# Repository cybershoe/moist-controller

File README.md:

# moist-controller
[![CC BY-SA 4.0][cc-by-sa-shield]][cc-by-sa]

## Overview

The Moisture-Optimization through Solar Technology (MOiST) Controller is a distributed, solar-powered, ESP8266-based
controller that exposes standard irrigation valves into [Home Assistant](https://www.home-assistant.io/) through
the [ESPHome](https://esphome.io/) component.

The MOiST valve is designed to be:

### Simple

The controller does one thing: control a valve. Once added into Home Assistant, the controller exposeses a switch that
opens or closes the valve, sensors for water flow rate and total water consumption, and battery power monitoring. That's
it. You are free to use whatever mechanism you want to manage the valves, including HA automations, Node-RED flows, or
any other platform that integratges with Home Assistant.

### Flexible

This project started because we change up our gardens frequently, and we couldn't predict in advance where we would want
automatic irrigation, or how the yard would be zoned. The idea behind the controller is that you can mount your valve, 
controller, and solar panel on a stake, stick it in the ground where you need it, point it South (or North if you're in
the Southern Hemisphere), hook it up to a hose and be up and running quickly. Buried valves with hardwired power look
nicer, and would be more appropriate for a lawn, but for a food garden, this design provides more flexibility. The
controller should be able to drive any standard irrigation valve that uses a 9V DC latching solenoid.

### Self-contained

Running hoses is one thing, running power is another. The controller was designed to minimize power consumption to a
point where it can run off of a 5-Watt, 6-Volt solar panel and a 18650 battery with the amount of sun available during
growing season. Components were selected for low quiescent power, and the most inefficient parts of the controller are
powered off unless actively being used. On a quiet WiFi network, power consumption averages around 30mA

## Usage

- Install a charged 18650 battery and press the "START" button to enable the battery protection circuit
- Connect a 3.3v USB to TTL adapter to the UART pin header JP1
- Install the ESPHome firmware with [this configuration](/moist-valve.yaml)
- Connect a 6V 1W solar panel to PV IN
- Connect your 9V latching irrigation valve solenoid to SOL
- Connect your water flow meter to METER
- Place the valve where the solar panel will receive full sun, connect your hoses, and begin MOiSTening your plants!

## Theory of Operation

The controller has 3 main functional areas: battery and power management, the solenoid driver, and the MCU.

### MCU (ESP8266)

The ESP8266 U5 is the heart of the system. It is running the ESPHome firmware, which handles the various outputs and sensors.
A bare ESP-WROOM-02D module was used rather than something like a D1 Mini, in order to remove unnecessary components and
minimize power requirements (USB-UART, LEDs, 5v regulator, etc.)

### Battery and Power Management

The system uses a standard 18560-style, unprotected Li-ion battery. Over-charge, over-discharge, over-current, and short
protection are provided by a BQ29733 protection IC U2, and solar charging is handled by a BQ24210 solar charger U1 in battery
tracking mode, to maximize charging ability with low solar panel outputs. The charger can take any 6-volt solar panel, and
will charge at up to 800 mA. An LP3693MPX LDO regulator U3 provides 3.3V to the the rest of the components. An INA219 I2C
wattmeter U5 monnitors the battery voltage and current flowing in/out of the battery.

### Solenoid Driver

The solenoid driver consists of an unregulated boost converter PS1 that raises the 3V3 rail up to ~9V, a capacitor C1 to store
enough energy to drive the solenoid, an H-bridge driver U6 to drive the solenoid in the appropriate direction, and a comparator 
U7 with an 8.2V reference D2 to indicate when the capacitor is sufficiently charged. To open or close the solenoid, the MCU first
sets the DRV_EN pin HIGH, which powers up the boost converter and enables the H-Bridge. After a short delay for the comparator
to stabilize, the MCU waits for the capacitor voltage to exceed the 8.2v reference, causing the comparator to bring the
!CHGD line LOW. Once the capacitor is charged, the MCU pulses the DRV_1 or DRV_2 pin HIGH for the appropriate duration to open or
close the valve, respectively, and then brings DRV_EN low to power off the driver circuitry and preserve energy.

## A Note about WiFi:

ESP power consumption is significantly affected (sometimes by a factor of 2 or more) by how long the modem can stay in sleep mode.
To minimize power consumption, consider the following:

- Increase your DTIM beacon interval. This increases how long the ESP can stay asleep before waking up to check for data.
- Broadcast traffic causes the modem to wake up, including mDNS. Consider creating a separate WLAN and subnet for your low-power ESP devices, and use static IPs in ESPHome to minimize the amount of broadcast traffic reaching the ESPs.

## Current status and next steps

### 2022-07-04
- Added solder jumper between GPIO16 and RST to allow deep sleep
- Redesigned board to fit Hammond 1555FF43GY enclosure
- Ordered redesigned boards (Rev 2.0A)

### 2022-07-04
- Working first revision hardware completed: [Video](https://youtu.be/AA5Or_j-FIE)
- Abandoned 3D printed custom enclosure, used off-the-shelf Hammond enclosure and a mounting plate for the Rev. 1.1B boards
- 3D printed a bracket to mount the solar panel at a 45° angle on a 3/4" square aluminium post

### 2021-11-18
- Fixed incorrect boot mode pull-up/down resistors
- Added reset button
- Renamed BOOT button to FLASH
- Added mounting hole instead of using 3d printed cantilever clips
- Ordered Rev 1.1B boards

### 2021-11-06:
The breadboard prototype is functionally complete, and an order has been placed with OSHPark for a batch of boards for a
final prototype. 

### TODO:
- NodeRED flows for irrigation timing
- Optimize board for smaller enclosure

This work is licensed under a
[Creative Commons Attribution-ShareAlike 4.0 International License][cc-by-sa].

[![CC BY-SA 4.0][cc-by-sa-image]][cc-by-sa]

[cc-by-sa]: http://creativecommons.org/licenses/by-sa/4.0/
[cc-by-sa-image]: https://licensebuttons.net/l/by-sa/4.0/88x31.png
[cc-by-sa-shield]: https://img.shields.io/badge/License-CC%20BY--SA%204.0-lightgrey.svg

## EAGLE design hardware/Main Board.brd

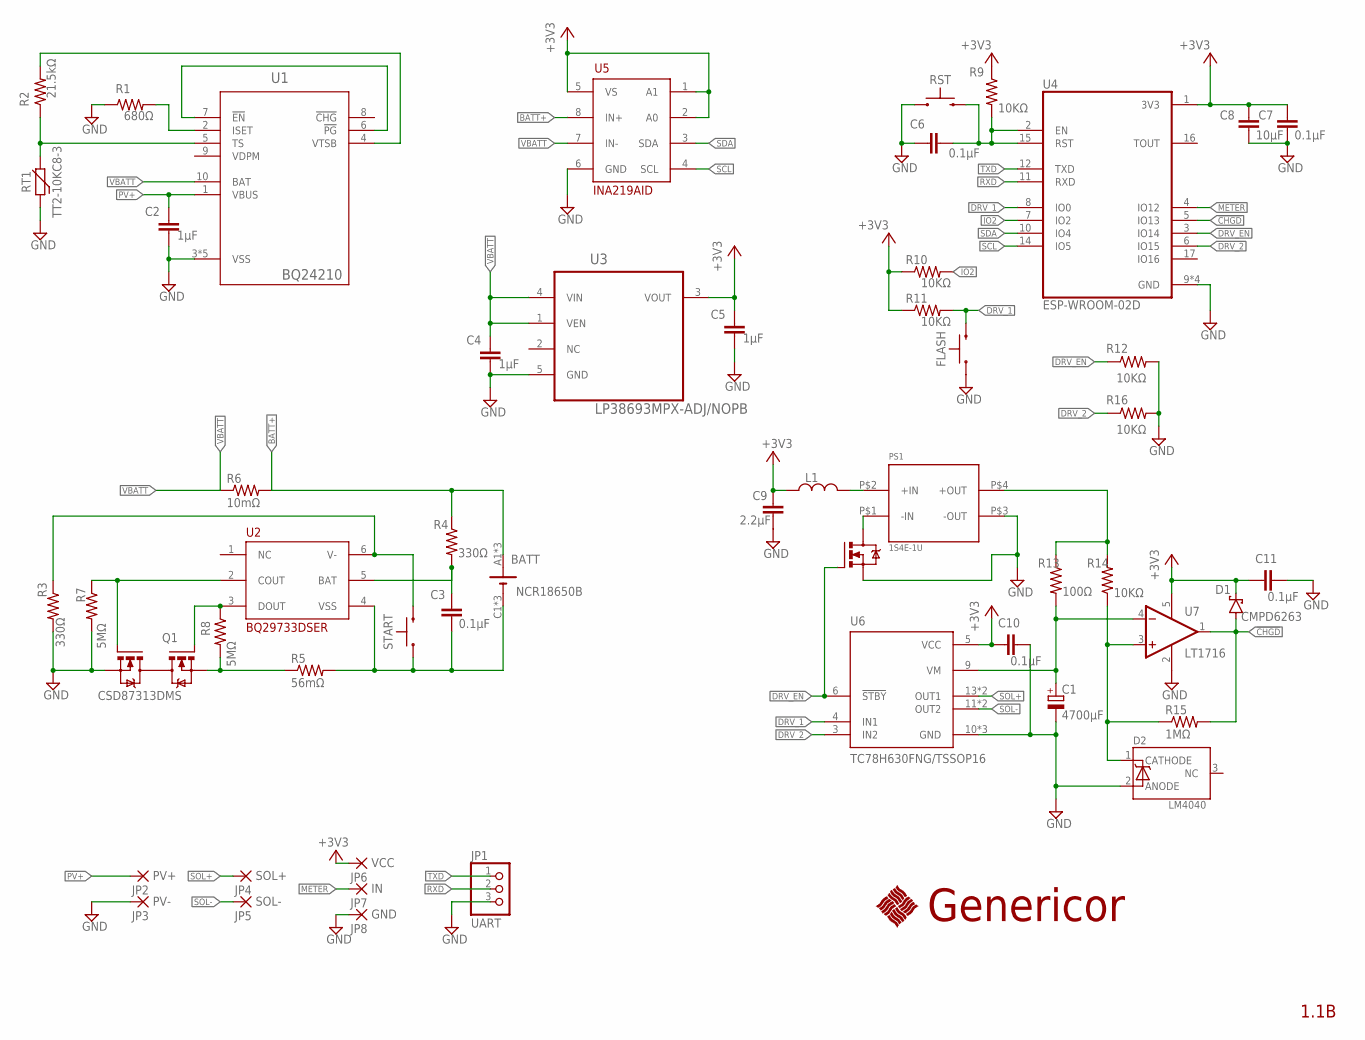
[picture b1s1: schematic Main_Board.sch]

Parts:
BATT: NCR18650B; 18650-65MM-54-PTH
C1: 4700µF; E7,5-18
C2, C4, C5: 1µF; C0402
C3, C6, C7, C10, C11: 0.1µF; C0402
C8: 10µF; C0805
C9: 2.2µF; C1210
D1: CMPD6263; SOT95P227X109-3N
D2: LM4040LM4040CIM3-8.2; SOT95P240X110-3N
FLASH: PTS636_SL43_SMTR_LFS; S_43
JP1: UART; 1X03
JP2: PV+; 2,54/1,1
JP3: PV-; 2,54/1,1
JP4: SOL+; 2,54/1,1
JP5: SOL-; 2,54/1,1
JP6: VCC; 2,54/1,1
JP7: IN; 2,54/1,1
JP8: GND; 2,54/1,1
L1: ASPI-6045S-180M-T; INDM6060X450N
PS1: 1S4E-1U; 1S4E_S1U-DIP4
Q1: CSD87313DMS; DMS0008A
Q2: CSD16406Q3; DQG0008A
R1: 680Ω; R0805
R2: 21.5kΩ; R0805
R3, R4: 330Ω; R0805
R5: 56mΩ; R0805
R6: 10mΩ; R1206
R7, R8: 5MΩ; R0805
R9, R10, R11, R12, R14, R16: 10KΩ; R0805
R13: 100Ω; R0805
R15: 1MΩ; R0805
RST: PTS636_SL43_SMTR_LFS; S_43
RT1: TT2-10KC8-3; THERMISTOR
START: PTS636_SL43_SMTR_LFS; S_43
U1: BQ24210; DQC10_P84X2P4
U2: BQ29733DSER; SON50P150X150X80-6N
U3: LP38693MPX-ADJ/NOPB; SOT150P700X180-5N
U4: ESP-WROOM-02D; MODULE_ESP-WROOM-02D
U5: INA219AID; SOIC127P599X175-8N
U6: TC78H630FNG/TSSOP16; TSSOP16
U7: LT1716; SOT95P280X100-5N
U$2: GENERICORLOGO

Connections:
8.2VREF: D2.1 (CATHODE), R14.1, R15.1, U7.3 (IN+)
9V+: PS1.P$4 (+OUT), R13.1, R14.2
!CHGD: D1.1 (A), R15.2, U4.5 (IO13), U7.1 (OUT)
+3V3: C5.1, C7.1, C8.1, C9.1, C10.1, C11.1, D1.3 (C), JP6.1, L1.1, R9.1, R10.1, R11.1, U3.3 (VOUT), U4.1 (3V3), U5.1 (A1), U5.2 (A0), U5.5 (VS), U6.5 (VCC), U7.5 (V+)
BAT: C3.1, R4.2, U2.5 (BAT)
BATT+: BATT.A1 (+), BATT.A2 (+), BATT.A3 (+), R4.1, R6.2, U5.8 (IN+)
BATT-: BATT.C1 (-), BATT.C2 (-), BATT.C3 (-), C3.2, R5.2, START.A (1), U2.4 (VSS)
COUT: Q1.4 (G2), R7.1, U2.2 (COUT)
DOUT: Q1.1 (G1), R8.1, U2.3 (DOUT)
DRV_1: FLASH.C (2), R11.2, U4.8 (IO0), U6.4 (IN1)
DRV_2: R16.1, U4.6 (IO15), U6.3 (IN2)
DRV_EN: Q2.4 (G), R12.1, U4.3 (IO14), U6.6 (!STBY)
EN-RST: C6.1, R9.2, RST.C (2), U4.2 (EN), U4.15 (RST)
GND: C1.-, C2.2, C4.2, C5.2, C6.2, C7.2, C8.2, C9.2, C10.2, C11.2, D2.2 (ANODE), FLASH.A (1), JP1.3, JP3.1, JP8.1, PS1.P$3 (-OUT), Q1.5 (S2), Q1.6 (S2), Q1.10 (S2), Q2.1 (S), Q2.2 (S), Q2.3 (S), R1.1, R3.2, R7.2, R12.2, R16.2, RST.A (1), RT1.1, U1.3 (VSS), U1.11 (VSS), U1.V (VSS), U1.V_1 (VSS), U1.V_2 (VSS), U3.5 (GND), U4.9 (GND), U4.13 (GND), U4.18 (GND), U4.19 (GND), U5.6 (GND), U6.10 (GND), U6.15 (GND), U6.16 (GND), U7.2 (V-)
IO2: R10.2, U4.7 (IO2)
ISET: R1.2, U1.2 (ISET)
METER: JP7.1, U4.4 (IO12)
PG-EN: U1.6 (!PG), U1.7 (!EN)
PS1+IN: L1.2, PS1.P$2 (+IN)
PS1-IN: PS1.P$1 (-IN), Q2.5 (D), Q2.6 (D), Q2.7 (D), Q2.8 (D), Q2.9 (D)
PV+: C2.1, JP2.1, U1.1 (VBUS)
Q1S1: Q1.7 (S1), Q1.8 (S1), Q1.9 (S1), R5.1, R8.2
RXD: JP1.2, U4.11 (RXD)
SCL: U4.14 (IO5), U5.4 (SCL)
SDA: U4.10 (IO4), U5.3 (SDA)
SOL+: JP4.1, U6.13 (OUT1), U6.14 (OUT1)
SOL-: JP5.1, U6.11 (OUT2), U6.12 (OUT2)
TS: R2.1, RT1.2, U1.5 (TS)
TXD: JP1.1, U4.12 (TXD)
V-: R3.1, START.C (2), U2.6 (V-)
VBATT: C4.1, R6.1, U1.10 (BAT), U3.1 (VEN), U3.4 (VIN), U5.7 (IN-)
VM: C1.+, R13.2, U6.9 (VM), U7.4 (IN-)
VTSB: R2.2, U1.4 (VTSB)

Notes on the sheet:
Genericor
1.1B

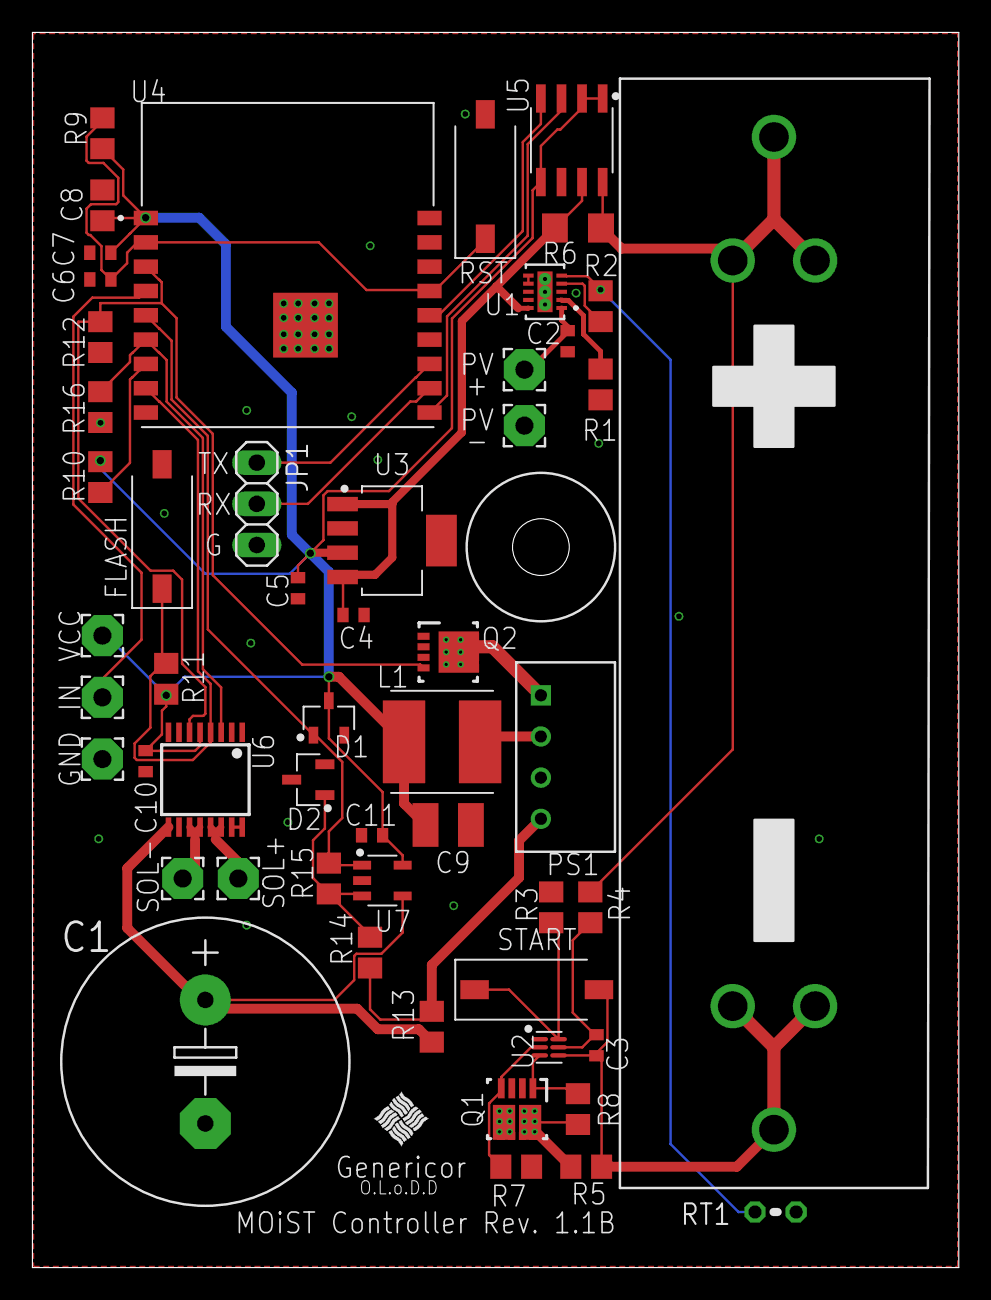
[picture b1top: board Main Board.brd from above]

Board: 2 copper layers, 57.1 x 76.2 mm, 54 parts (0 on the bottom side), 33 nets.

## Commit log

2021-11-06 Create Main_Board.svg
    Add SVG of Schematic
2021-11-06 Update Docs
2021-11-06 Add WiFi power note
2021-11-06 Typo
2021-11-06 Typos
2021-11-06 Fix date format
2021-11-07 Update mainboard graphic
2021-11-07 Missing underscore
2021-11-08 Move hardware, add example config
2021-11-08 Stopped typing halfway through
2021-11-08 Indentation error in YAML
2021-11-08 Add UART pinout
2021-11-08 Pin swap in docs
2021-11-18 Update docs for Rev 1.1B changes
2021-11-18 Accidental tabs in YAML
2022-02-10 Initialize repo
2022-07-04 1st fully-functional valve
2022-07-04 Added video link
2022-07-08 2.0A docs
